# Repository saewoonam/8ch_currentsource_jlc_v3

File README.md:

# 8ch_currentsource_jlc_v3
Second attempt to make an 8 channel current bias board.  
#  Change from v2
- Added a voltage regulator for each channel

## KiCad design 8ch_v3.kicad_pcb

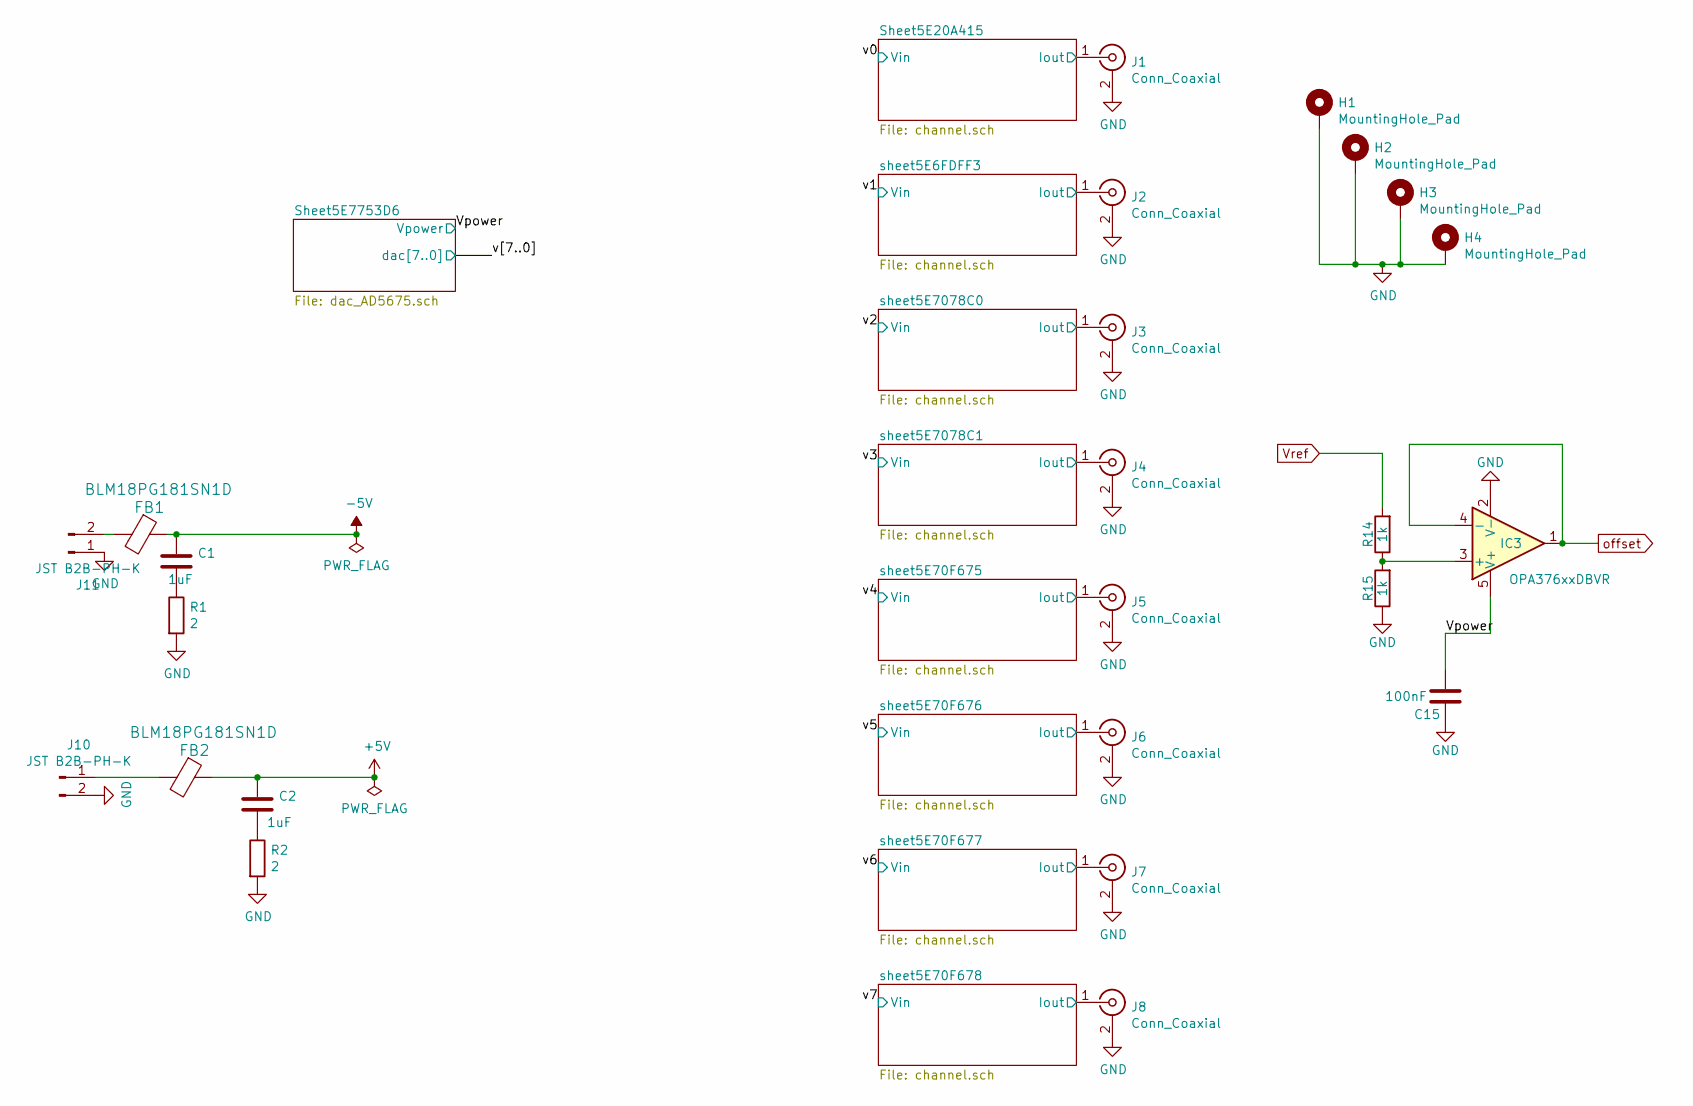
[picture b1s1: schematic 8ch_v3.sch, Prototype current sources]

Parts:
C1, C2: 1uF; C_0603_1608Metric_Pad1.05x0.95mm_HandSolder; MPN CL10B105KA8NNNC
C15: 100nF; C_0603_1608Metric_Pad1.05x0.95mm_HandSolder; MPN CC0603KPX7R7BB104; Digikey 490-1767-1-ND
FB1, FB2: BLM18PG181SN1D; L_0603_1608Metric_Pad1.05x0.95mm_HandSolder; MPN BLM18PG181SN1D
H1, H2, H3, H4: MountingHole_Pad; MountingHole_3.2mm_M3_Pad_Via
IC3: OPA376xxDBVR; SOT-23-5; MPN OPA376AIDBVR
J1, J2, J3, J4, J5, J6, J7, J8: Conn_Coaxial; RF_SMA_Vertical_5-1814832-1; MPN CONSMA001-SMD-G
J10, J11: JST B2B-PH-K; JST_PH_B2B-PH-K_1x02_P2.00mm_Vertical; MPN S2B-PH-SM4
R1, R2: 2; R_0603_1608Metric_Pad1.05x0.95mm_HandSolder; MPN 0603WAF200KT5E
R14, R15: 1k; R_0603_1608Metric_Pad1.05x0.95mm_HandSolder; MPN RC0603FR-071KL

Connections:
+5V: C2.1, FB2.1; also elsewhere on the board
-5V: C1.1, FB1.1; also elsewhere on the board
/Sheet5E20A415/Iout: J1.1 (In); also elsewhere on the board
/Vpower: C15.2, IC3.5 (V+); also elsewhere on the board
/sheet5E6FDFF3/Iout: J2.1 (In); also elsewhere on the board
/sheet5E70F675/Iout: J5.1 (In); also elsewhere on the board
/sheet5E70F676/Iout: J6.1 (In); also elsewhere on the board
/sheet5E70F677/Iout: J7.1 (In); also elsewhere on the board
/sheet5E70F678/Iout: J8.1 (In); also elsewhere on the board
/sheet5E7078C0/Iout: J3.1 (In); also elsewhere on the board
/sheet5E7078C1/Iout: J4.1 (In); also elsewhere on the board
GND: C15.1, H1.1, H2.1, H3.1, H4.1, IC3.2 (V-), J1.2 (Ext), J2.2 (Ext), J3.2 (Ext), J4.2 (Ext), J5.2 (Ext), J6.2 (Ext), J7.2 (Ext), J8.2 (Ext), J10.2, J11.1, R1.2, R2.2, R15.1; also elsewhere on the board
unnamed: C1.2, R1.1
unnamed: C2.2, R2.1
unnamed: FB1.2, J11.2
unnamed: FB2.2, J10.1
unnamed: IC3.3 (+), R14.1, R15.2
Vref: R14.2; also elsewhere on the board
offset: IC3.1, IC3.4 (-); also elsewhere on the board

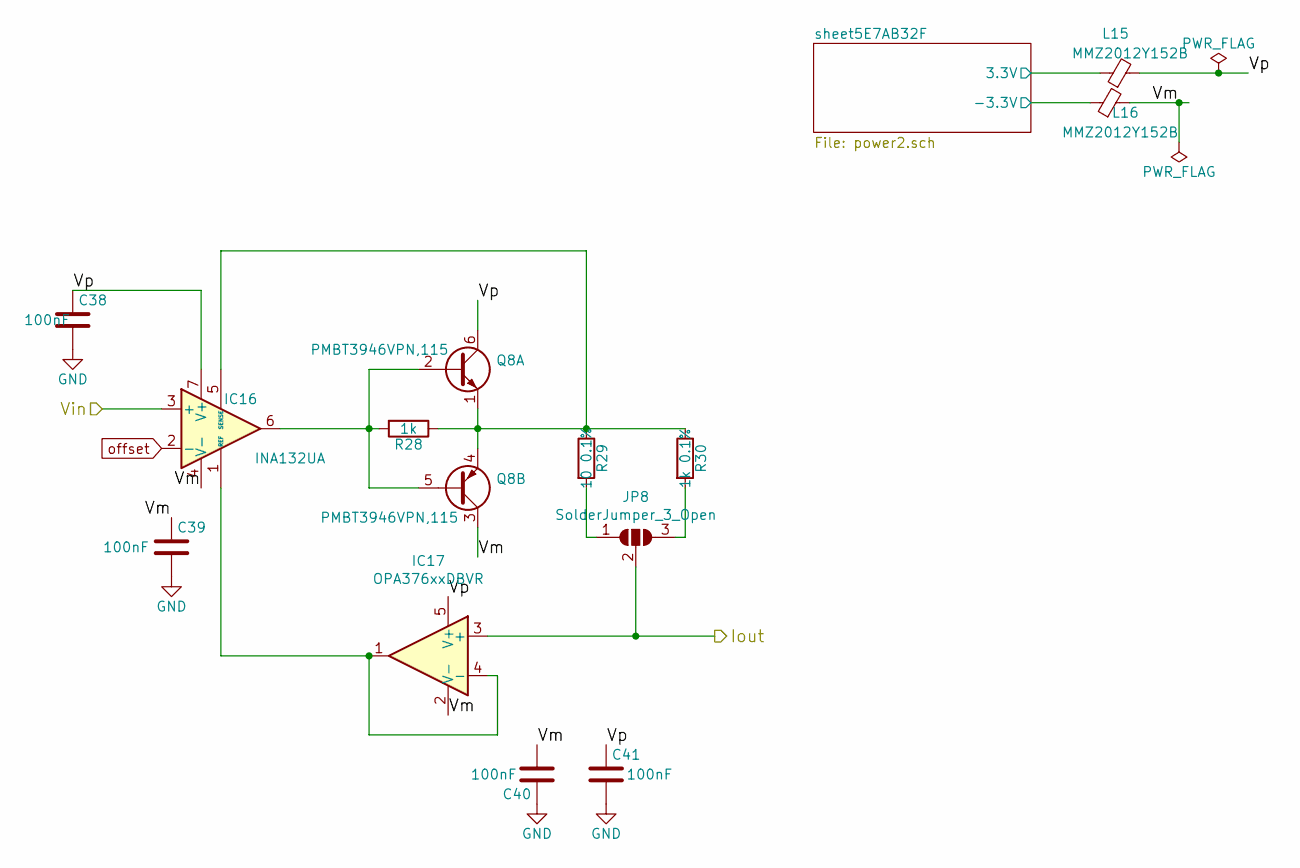
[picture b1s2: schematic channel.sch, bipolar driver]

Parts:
C7, C8, C9, C10: 100nF; C_0603_1608Metric_Pad1.05x0.95mm_HandSolder; Part GRM31C5C1E104JA01L; Digikey 490-1767-1-ND
IC1: INA132UA; SOIC-8_3.9x4.9mm_P1.27mm; MPN-backup AD8276ARMZ; LCSC C38199
IC2: OPA376xxDBVR; SOT-23-5; MPN OPA376AIDBVR; LCSC C42314
JP1: SolderJumper_3_Open; SolderJumper-3_P1.3mm_Open_Pad1.0x1.5mm
L1, L2: MMZ2012Y152B; L_0805_2012Metric_Pad1.15x1.40mm_HandSolder; MPN MMZ2012Y152BTD25
Q1: PMBT3946VPN,115; SOT-363_SC-70-6; MPN MMDT3946-7-F; LCSC C151354
R3: 1k; R_0603_1608Metric_Pad1.05x0.95mm_HandSolder; MPN RC0603FR-071KL
R4: 10 0.1%; R_0805_2012Metric; MPN 2-1625868-7
R5: 1k 0.1%; R_0805_2012Metric; MPN ERA-6AEB102V

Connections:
/Sheet5E20A415/Iout: IC2.3 (+), JP1.2 (C); also elsewhere on the board
/Sheet5E20A415/Vm: C8.1, C9.2, IC1.4 (V-), IC2.2 (V-), L2.2, Q1.3 (C2)
/Sheet5E20A415/Vp: C7.1, C10.1, IC1.7 (V+), IC2.5 (V+), L1.2, Q1.6 (C1)
/Sheet5E20A415/sheet5E7AB32F/3.3V: L1.1; also elsewhere on the board
/Sheet5E20A415/sheet5E7AB32F/-3.3V: L2.1; also elsewhere on the board
/v0: IC1.3 (+); also elsewhere on the board
GND: C7.2, C8.2, C9.1, C10.2; also elsewhere on the board
unnamed: IC1.1 (REF), IC2.1, IC2.4 (-)
unnamed: IC1.5 (SENSE), Q1.1 (E1), Q1.4 (E2), R3.1, R4.1, R5.1
unnamed: IC1.6, Q1.2 (B1), Q1.5 (B2), R3.2
unnamed: JP1.1 (A), R4.2
unnamed: JP1.3 (B), R5.2
offset: IC1.2 (-); also elsewhere on the board

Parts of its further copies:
C11, C12, C16, C17, C18, C19, C20, C21, C22, C23, C24, C25, C26, C27, C28, C29, C30, C31, C32, C33, C34, C35, C36, C37, C38, C39, C40, C41: 100nF; C_0603_1608Metric_Pad1.05x0.95mm_HandSolder; Part GRM31C5C1E104JA01L; Digikey 490-1767-1-ND
IC4, IC6, IC8, IC10, IC12, IC14, IC16: INA132UA; SOIC-8_3.9x4.9mm_P1.27mm; MPN-backup AD8276ARMZ; LCSC C38199
IC5, IC7, IC9, IC11, IC13, IC15, IC17: OPA376xxDBVR; SOT-23-5; MPN OPA376AIDBVR; LCSC C42314
JP2, JP3, JP4, JP5, JP6, JP7, JP8: SolderJumper_3_Open; SolderJumper-3_P1.3mm_Open_Pad1.0x1.5mm
L3, L4, L5, L6, L7, L8, L9, L10, L11, L12, L13, L14, L15, L16: MMZ2012Y152B; L_0805_2012Metric_Pad1.15x1.40mm_HandSolder; MPN MMZ2012Y152BTD25
Q2, Q3, Q4, Q5, Q6, Q7, Q8: PMBT3946VPN,115; SOT-363_SC-70-6; MPN MMDT3946-7-F; LCSC C151354
R6, R9, R16, R19, R22, R25, R28: 1k; R_0603_1608Metric_Pad1.05x0.95mm_HandSolder; MPN RC0603FR-071KL
R7, R10, R17, R20, R23, R26, R29: 10 0.1%; R_0805_2012Metric; MPN 2-1625868-7
R8, R11, R18, R21, R24, R27, R30: 1k 0.1%; R_0805_2012Metric; MPN ERA-6AEB102V

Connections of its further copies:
/sheet5E6FDFF3/Iout: IC5.3 (+), JP2.2 (C); also elsewhere on the board
/sheet5E6FDFF3/Vm: C12.1, C16.2, IC4.4 (V-), IC5.2 (V-), L4.2, Q2.3 (C2)
/sheet5E6FDFF3/Vp: C11.1, C17.1, IC4.7 (V+), IC5.5 (V+), L3.2, Q2.6 (C1)
/sheet5E6FDFF3/sheet5E7AB32F/3.3V: L3.1; also elsewhere on the board
/sheet5E6FDFF3/sheet5E7AB32F/-3.3V: L4.1; also elsewhere on the board
/sheet5E70F675/Iout: IC11.3 (+), JP5.2 (C); also elsewhere on the board
/sheet5E70F675/Vm: C27.1, C28.2, IC10.4 (V-), IC11.2 (V-), L10.2, Q5.3 (C2)
/sheet5E70F675/Vp: C26.1, C29.1, IC10.7 (V+), IC11.5 (V+), L9.2, Q5.6 (C1)
/sheet5E70F675/sheet5E7AB32F/3.3V: L9.1; also elsewhere on the board
/sheet5E70F675/sheet5E7AB32F/-3.3V: L10.1; also elsewhere on the board
/sheet5E70F676/Iout: IC13.3 (+), JP6.2 (C); also elsewhere on the board
/sheet5E70F676/Vm: C31.1, C32.2, IC12.4 (V-), IC13.2 (V-), L12.2, Q6.3 (C2)
/sheet5E70F676/Vp: C30.1, C33.1, IC12.7 (V+), IC13.5 (V+), L11.2, Q6.6 (C1)
/sheet5E70F676/sheet5E7AB32F/3.3V: L11.1; also elsewhere on the board
/sheet5E70F676/sheet5E7AB32F/-3.3V: L12.1; also elsewhere on the board
/sheet5E70F677/Iout: IC15.3 (+), JP7.2 (C); also elsewhere on the board
/sheet5E70F677/Vm: C35.1, C36.2, IC14.4 (V-), IC15.2 (V-), L14.2, Q7.3 (C2)
/sheet5E70F677/Vp: C34.1, C37.1, IC14.7 (V+), IC15.5 (V+), L13.2, Q7.6 (C1)
/sheet5E70F677/sheet5E7AB32F/3.3V: L13.1; also elsewhere on the board
/sheet5E70F677/sheet5E7AB32F/-3.3V: L14.1; also elsewhere on the board
/sheet5E70F678/Iout: IC17.3 (+), JP8.2 (C); also elsewhere on the board
/sheet5E70F678/Vm: C39.1, C40.2, IC16.4 (V-), IC17.2 (V-), L16.2, Q8.3 (C2)
/sheet5E70F678/Vp: C38.1, C41.1, IC16.7 (V+), IC17.5 (V+), L15.2, Q8.6 (C1)
/sheet5E70F678/sheet5E7AB32F/3.3V: L15.1; also elsewhere on the board
/sheet5E70F678/sheet5E7AB32F/-3.3V: L16.1; also elsewhere on the board
/sheet5E7078C0/Iout: IC7.3 (+), JP3.2 (C); also elsewhere on the board
/sheet5E7078C0/Vm: C19.1, C20.2, IC6.4 (V-), IC7.2 (V-), L6.2, Q3.3 (C2)
/sheet5E7078C0/Vp: C18.1, C21.1, IC6.7 (V+), IC7.5 (V+), L5.2, Q3.6 (C1)
/sheet5E7078C0/sheet5E7AB32F/3.3V: L5.1; also elsewhere on the board
/sheet5E7078C0/sheet5E7AB32F/-3.3V: L6.1; also elsewhere on the board
/sheet5E7078C1/Iout: IC9.3 (+), JP4.2 (C); also elsewhere on the board
/sheet5E7078C1/Vm: C23.1, C24.2, IC8.4 (V-), IC9.2 (V-), L8.2, Q4.3 (C2)
/sheet5E7078C1/Vp: C22.1, C25.1, IC8.7 (V+), IC9.5 (V+), L7.2, Q4.6 (C1)
/sheet5E7078C1/sheet5E7AB32F/3.3V: L7.1; also elsewhere on the board
/sheet5E7078C1/sheet5E7AB32F/-3.3V: L8.1; also elsewhere on the board
/v1: IC4.3 (+); also elsewhere on the board
/v2: IC6.3 (+); also elsewhere on the board
/v3: IC8.3 (+); also elsewhere on the board
/v4: IC10.3 (+); also elsewhere on the board
/v5: IC12.3 (+); also elsewhere on the board
/v6: IC14.3 (+); also elsewhere on the board
/v7: IC16.3 (+); also elsewhere on the board
GND: C11.2, C12.2, C16.1, C17.2, C18.2, C19.2, C20.1, C21.2, C22.2, C23.2, C24.1, C25.2, C26.2, C27.2, C28.1, C29.2, C30.2, C31.2, C32.1, C33.2, C34.2, C35.2, C36.1, C37.2, C38.2, C39.2, C40.1, C41.2; also elsewhere on the board
unnamed: IC4.1 (REF), IC5.1, IC5.4 (-)
unnamed: IC4.5 (SENSE), Q2.1 (E1), Q2.4 (E2), R6.1, R7.1, R8.1
unnamed: IC4.6, Q2.2 (B1), Q2.5 (B2), R6.2
unnamed: IC6.1 (REF), IC7.1, IC7.4 (-)
unnamed: IC6.5 (SENSE), Q3.1 (E1), Q3.4 (E2), R9.1, R10.1, R11.1
unnamed: IC6.6, Q3.2 (B1), Q3.5 (B2), R9.2
unnamed: IC8.1 (REF), IC9.1, IC9.4 (-)
unnamed: IC8.5 (SENSE), Q4.1 (E1), Q4.4 (E2), R16.1, R17.1, R18.1
unnamed: IC8.6, Q4.2 (B1), Q4.5 (B2), R16.2
unnamed: IC10.1 (REF), IC11.1, IC11.4 (-)
unnamed: IC10.5 (SENSE), Q5.1 (E1), Q5.4 (E2), R19.1, R20.1, R21.1
unnamed: IC10.6, Q5.2 (B1), Q5.5 (B2), R19.2
unnamed: IC12.1 (REF), IC13.1, IC13.4 (-)
unnamed: IC12.5 (SENSE), Q6.1 (E1), Q6.4 (E2), R22.1, R23.1, R24.1
unnamed: IC12.6, Q6.2 (B1), Q6.5 (B2), R22.2
unnamed: IC14.1 (REF), IC15.1, IC15.4 (-)
unnamed: IC14.5 (SENSE), Q7.1 (E1), Q7.4 (E2), R25.1, R26.1, R27.1
unnamed: IC14.6, Q7.2 (B1), Q7.5 (B2), R25.2
unnamed: IC16.1 (REF), IC17.1, IC17.4 (-)
unnamed: IC16.5 (SENSE), Q8.1 (E1), Q8.4 (E2), R28.1, R29.1, R30.1
unnamed: IC16.6, Q8.2 (B1), Q8.5 (B2), R28.2
unnamed: JP2.1 (A), R7.2
unnamed: JP2.3 (B), R8.2
unnamed: JP3.1 (A), R10.2
unnamed: JP3.3 (B), R11.2
unnamed: JP4.1 (A), R17.2
unnamed: JP4.3 (B), R18.2
unnamed: JP5.1 (A), R20.2
unnamed: JP5.3 (B), R21.2
unnamed: JP6.1 (A), R23.2
unnamed: JP6.3 (B), R24.2
unnamed: JP7.1 (A), R26.2
unnamed: JP7.3 (B), R27.2
unnamed: JP8.1 (A), R29.2
unnamed: JP8.3 (B), R30.2
offset: IC4.2 (-), IC6.2 (-), IC8.2 (-), IC10.2 (-), IC12.2 (-), IC14.2 (-), IC16.2 (-); also elsewhere on the board

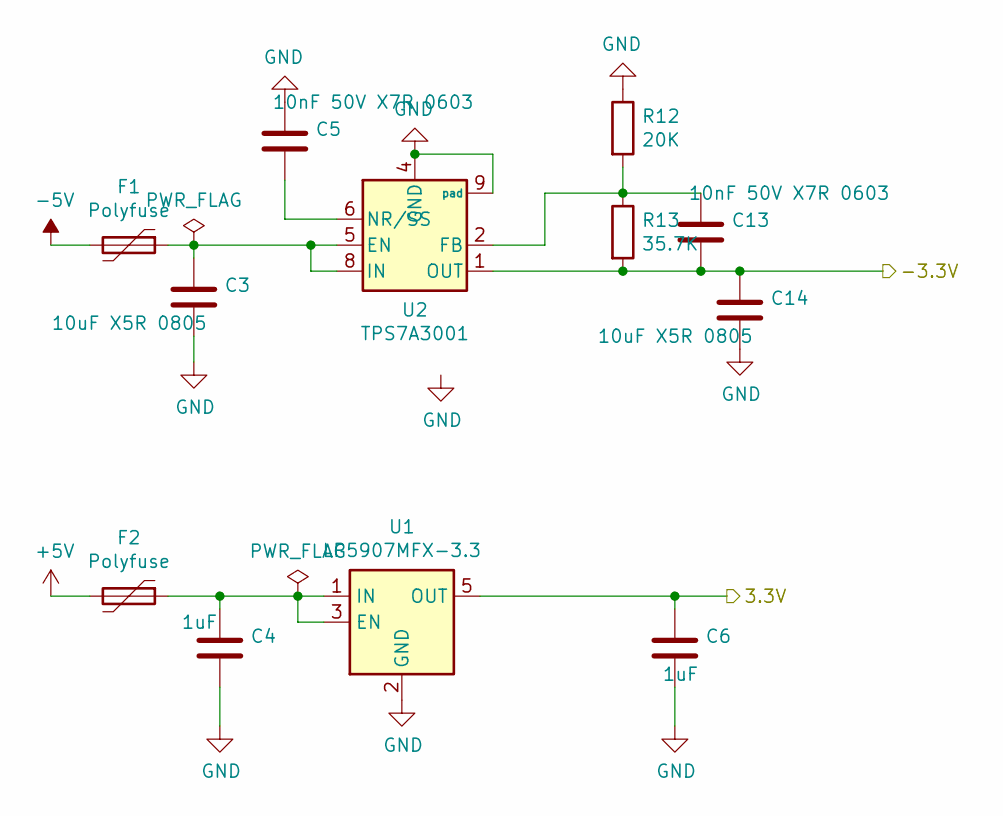
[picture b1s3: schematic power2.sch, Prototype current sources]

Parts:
C3, C14: 10uF X5R 0805; C_0805_2012Metric_Pad1.15x1.40mm_HandSolder; MPN CL31B106KBHNNNE
C4, C6: 1uF; C_0603_1608Metric_Pad1.05x0.95mm_HandSolder; MPN CL10B105KA8NNNC
C5, C13: 10nF 50V X7R 0603; C_0603_1608Metric_Pad1.05x0.95mm_HandSolder; MPN 0603B103K500NT
F1, F2: Polyfuse; Fuse_0603_1608Metric_Pad1.05x0.95mm_HandSolder
R12: 20K; R_0603_1608Metric_Pad1.05x0.95mm_HandSolder; MPN 0603WAF2002T5E
R13: 35.7K; R_0603_1608Metric_Pad1.05x0.95mm_HandSolder; MPN 0603WAF3572T5E
U1: LP5907MFX-3.3; SOT-23-5; MPN LP5907MFX-3.3
U2: TPS7A3001; MSOP-8-1EP_3x3mm_P0.65mm_EP1.68x1.88mm; MPN TPS7A3001DGNR

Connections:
+5V: F2.2; also elsewhere on the board
-5V: F1.2; also elsewhere on the board
/Sheet5E20A415/sheet5E7AB32F/3.3V: C6.1, U1.5 (OUT); also elsewhere on the board
/Sheet5E20A415/sheet5E7AB32F/-3.3V: C13.2, C14.1, R13.2, U2.1 (OUT); also elsewhere on the board
GND: C3.2, C4.2, C5.1, C6.2, C14.2, R12.1, U1.2 (GND), U2.4 (GND), U2.9 (pad); also elsewhere on the board
unnamed: C3.1, F1.1, U2.5 (EN), U2.8 (IN)
unnamed: C4.1, F2.1, U1.1 (IN), U1.3 (EN)
unnamed: C5.2, U2.6 (NR/SS)
unnamed: C13.1, R12.2, R13.1, U2.2 (FB)

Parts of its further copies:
C46, C51, C52, C57, C58, C63, C64, C69, C70, C75, C76, C81, C82, C87: 10uF X5R 0805; C_0805_2012Metric_Pad1.15x1.40mm_HandSolder; MPN CL31B106KBHNNNE
C47, C49, C53, C55, C59, C61, C65, C67, C71, C73, C77, C79, C83, C85: 1uF; C_0603_1608Metric_Pad1.05x0.95mm_HandSolder; MPN CL10B105KA8NNNC
C48, C50, C54, C56, C60, C62, C66, C68, C72, C74, C78, C80, C84, C86: 10nF 50V X7R 0603; C_0603_1608Metric_Pad1.05x0.95mm_HandSolder; MPN 0603B103K500NT
F3, F4, F5, F6, F7, F8, F9, F10, F11, F12, F13, F14, F15, F16: Polyfuse; Fuse_0603_1608Metric_Pad1.05x0.95mm_HandSolder
R33, R35, R37, R39, R41, R43, R45: 20K; R_0603_1608Metric_Pad1.05x0.95mm_HandSolder; MPN 0603WAF2002T5E
R34, R36, R38, R40, R42, R44, R46: 35.7K; R_0603_1608Metric_Pad1.05x0.95mm_HandSolder; MPN 0603WAF3572T5E
U3, U5, U7, U9, U11, U13, U15: LP5907MFX-3.3; SOT-23-5; MPN LP5907MFX-3.3
U4, U6, U8, U10, U12, U14, U16: TPS7A3001; MSOP-8-1EP_3x3mm_P0.65mm_EP1.68x1.88mm; MPN TPS7A3001DGNR

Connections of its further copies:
+5V: F4.2, F6.2, F8.2, F10.2, F12.2, F14.2, F16.2; also elsewhere on the board
-5V: F3.2, F5.2, F7.2, F9.2, F11.2, F13.2, F15.2; also elsewhere on the board
/sheet5E6FDFF3/sheet5E7AB32F/3.3V: C49.1, U3.5 (OUT); also elsewhere on the board
/sheet5E6FDFF3/sheet5E7AB32F/-3.3V: C50.2, C51.1, R34.2, U4.1 (OUT); also elsewhere on the board
/sheet5E70F675/sheet5E7AB32F/3.3V: C67.1, U9.5 (OUT); also elsewhere on the board
/sheet5E70F675/sheet5E7AB32F/-3.3V: C68.2, C69.1, R40.2, U10.1 (OUT); also elsewhere on the board
/sheet5E70F676/sheet5E7AB32F/3.3V: C73.1, U11.5 (OUT); also elsewhere on the board
/sheet5E70F676/sheet5E7AB32F/-3.3V: C74.2, C75.1, R42.2, U12.1 (OUT); also elsewhere on the board
/sheet5E70F677/sheet5E7AB32F/3.3V: C79.1, U13.5 (OUT); also elsewhere on the board
/sheet5E70F677/sheet5E7AB32F/-3.3V: C80.2, C81.1, R44.2, U14.1 (OUT); also elsewhere on the board
/sheet5E70F678/sheet5E7AB32F/3.3V: C85.1, U15.5 (OUT); also elsewhere on the board
/sheet5E70F678/sheet5E7AB32F/-3.3V: C86.2, C87.1, R46.2, U16.1 (OUT); also elsewhere on the board
/sheet5E7078C0/sheet5E7AB32F/3.3V: C55.1, U5.5 (OUT); also elsewhere on the board
/sheet5E7078C0/sheet5E7AB32F/-3.3V: C56.2, C57.1, R36.2, U6.1 (OUT); also elsewhere on the board
/sheet5E7078C1/sheet5E7AB32F/3.3V: C61.1, U7.5 (OUT); also elsewhere on the board
/sheet5E7078C1/sheet5E7AB32F/-3.3V: C62.2, C63.1, R38.2, U8.1 (OUT); also elsewhere on the board
GND: C46.2, C47.2, C48.1, C49.2, C51.2, C52.2, C53.2, C54.1, C55.2, C57.2, C58.2, C59.2, C60.1, C61.2, C63.2, C64.2, C65.2, C66.1, C67.2, C69.2, C70.2, C71.2, C72.1, C73.2, C75.2, C76.2, C77.2, C78.1, C79.2, C81.2, C82.2, C83.2, C84.1, C85.2, C87.2, R33.1, R35.1, R37.1, R39.1, R41.1, R43.1, R45.1, U3.2 (GND), U4.4 (GND), U4.9 (pad), U5.2 (GND), U6.4 (GND), U6.9 (pad), U7.2 (GND), U8.4 (GND), U8.9 (pad), U9.2 (GND), U10.4 (GND), U10.9 (pad), U11.2 (GND), U12.4 (GND), U12.9 (pad), U13.2 (GND), U14.4 (GND), U14.9 (pad), U15.2 (GND), U16.4 (GND), U16.9 (pad); also elsewhere on the board
unnamed: C46.1, F3.1, U4.5 (EN), U4.8 (IN)
unnamed: C47.1, F4.1, U3.1 (IN), U3.3 (EN)
unnamed: C48.2, U4.6 (NR/SS)
unnamed: C50.1, R33.2, R34.1, U4.2 (FB)
unnamed: C52.1, F5.1, U6.5 (EN), U6.8 (IN)
unnamed: C53.1, F6.1, U5.1 (IN), U5.3 (EN)
unnamed: C54.2, U6.6 (NR/SS)
unnamed: C56.1, R35.2, R36.1, U6.2 (FB)
unnamed: C58.1, F7.1, U8.5 (EN), U8.8 (IN)
unnamed: C59.1, F8.1, U7.1 (IN), U7.3 (EN)
unnamed: C60.2, U8.6 (NR/SS)
unnamed: C62.1, R37.2, R38.1, U8.2 (FB)
unnamed: C64.1, F9.1, U10.5 (EN), U10.8 (IN)
unnamed: C65.1, F10.1, U9.1 (IN), U9.3 (EN)
unnamed: C66.2, U10.6 (NR/SS)
unnamed: C68.1, R39.2, R40.1, U10.2 (FB)
unnamed: C70.1, F11.1, U12.5 (EN), U12.8 (IN)
unnamed: C71.1, F12.1, U11.1 (IN), U11.3 (EN)
unnamed: C72.2, U12.6 (NR/SS)
unnamed: C74.1, R41.2, R42.1, U12.2 (FB)
unnamed: C76.1, F13.1, U14.5 (EN), U14.8 (IN)
unnamed: C77.1, F14.1, U13.1 (IN), U13.3 (EN)
unnamed: C78.2, U14.6 (NR/SS)
unnamed: C80.1, R43.2, R44.1, U14.2 (FB)
unnamed: C82.1, F15.1, U16.5 (EN), U16.8 (IN)
unnamed: C83.1, F16.1, U15.1 (IN), U15.3 (EN)
unnamed: C84.2, U16.6 (NR/SS)
unnamed: C86.1, R45.2, R46.1, U16.2 (FB)

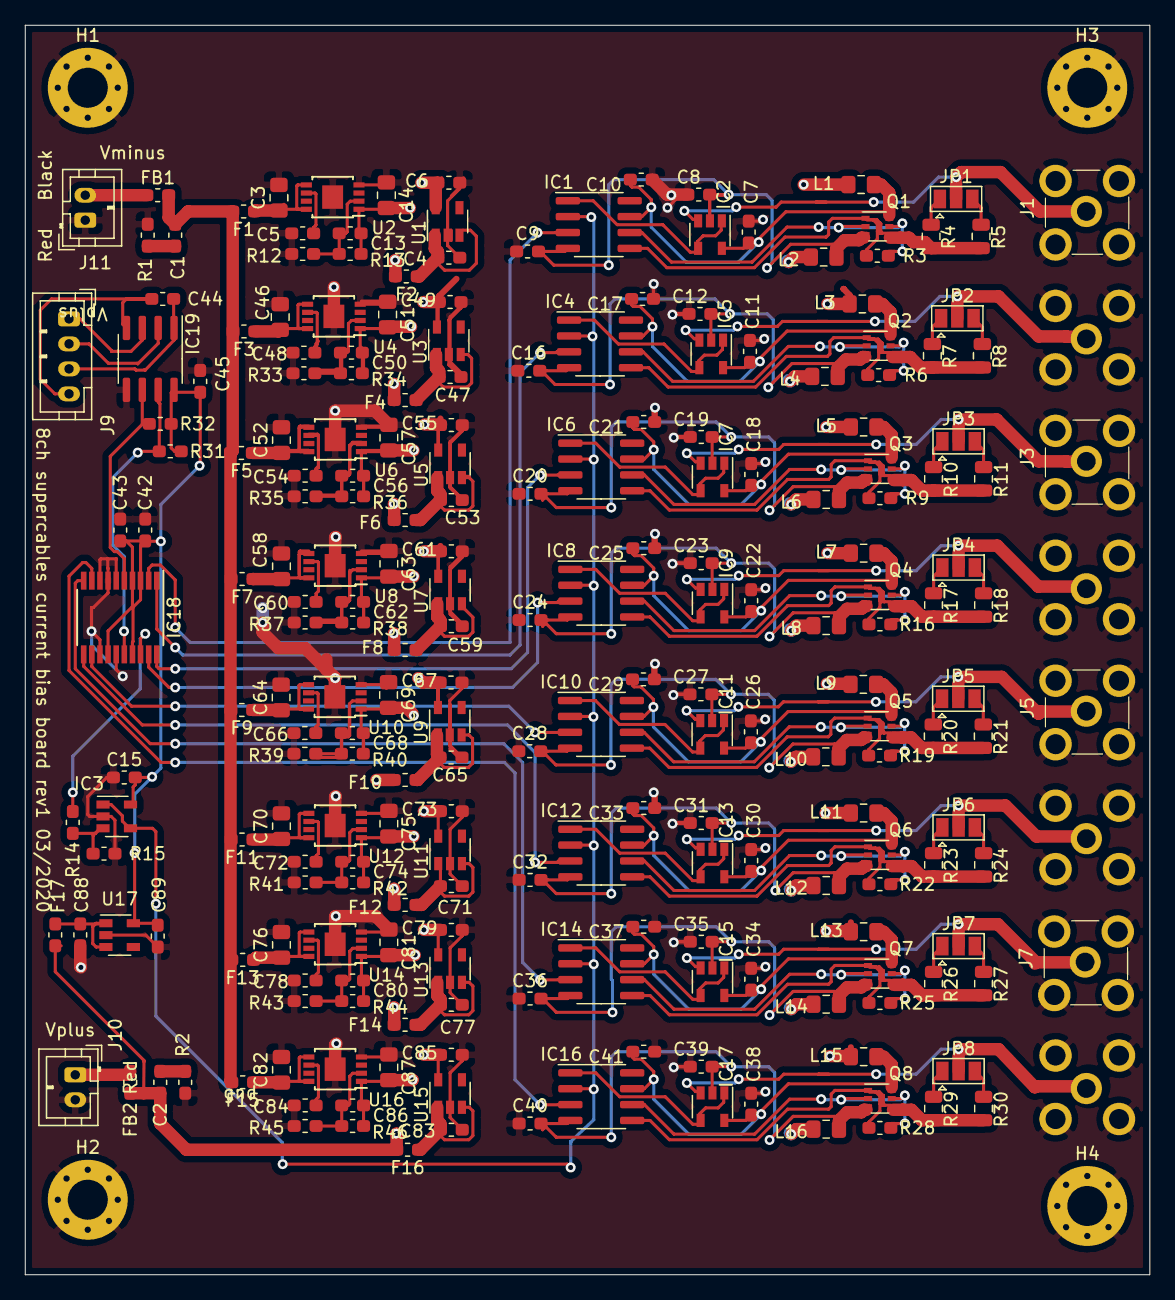
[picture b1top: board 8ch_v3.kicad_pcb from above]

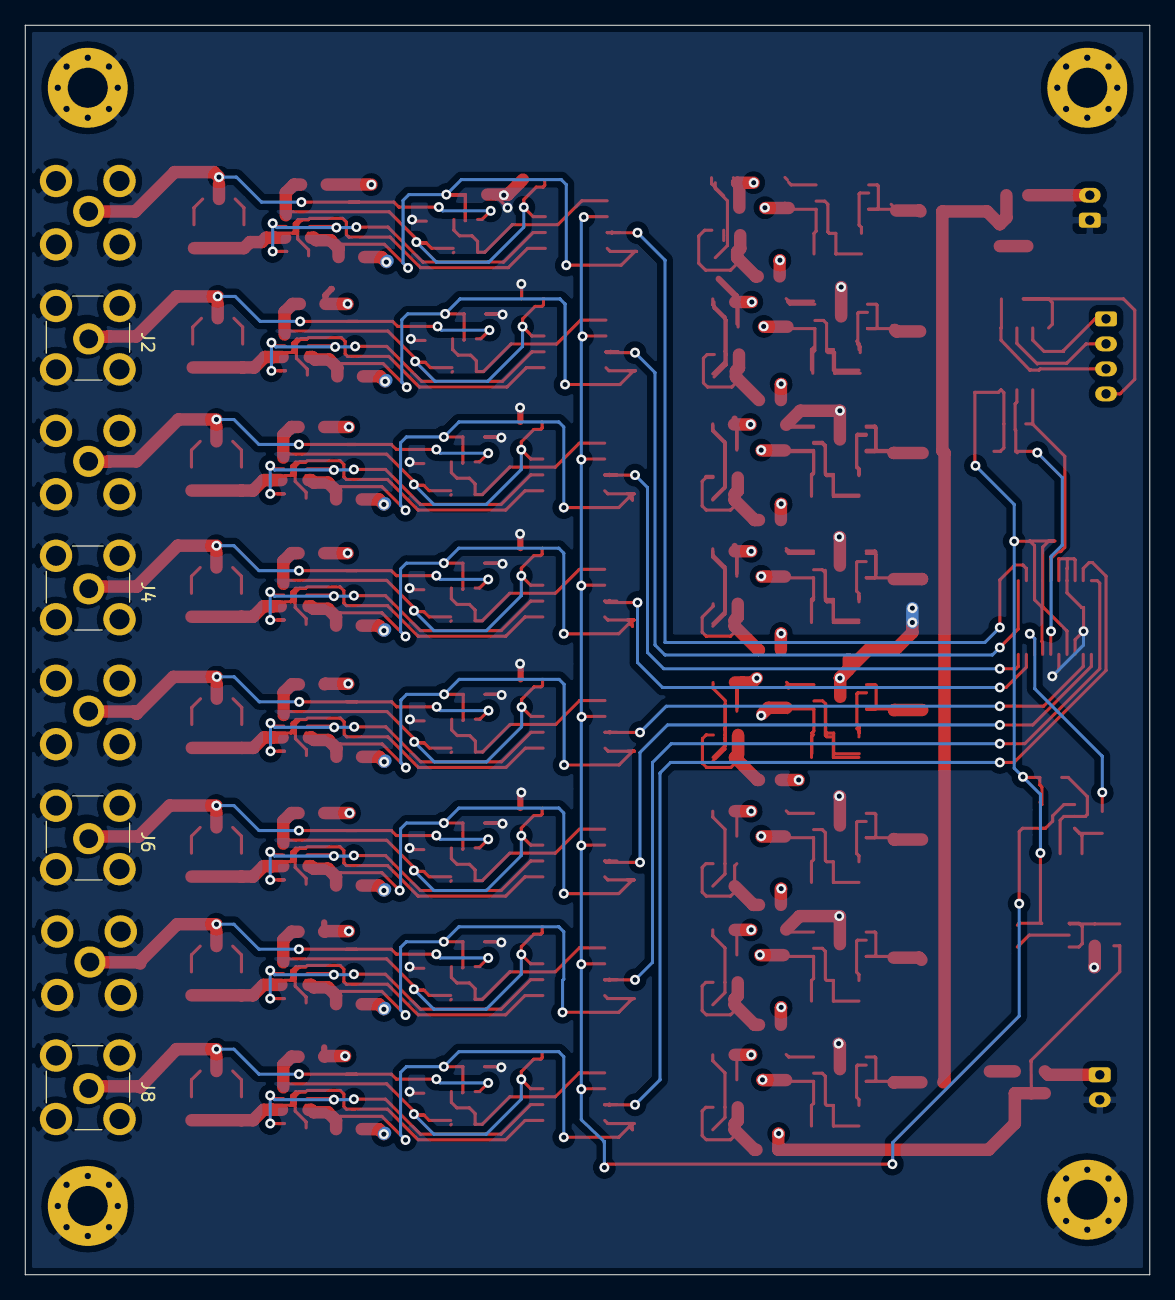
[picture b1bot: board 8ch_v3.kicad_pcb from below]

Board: 4 copper layers, 90.0 x 100.0 mm, 237 parts (4 on the bottom side), 138 nets.

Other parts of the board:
C42, C43, C44, C45: 100nF; C_0603_1608Metric_Pad1.05x0.95mm_HandSolder
C88, C89: 1uF; C_0603_1608Metric_Pad1.05x0.95mm_HandSolder
F17: Polyfuse; Fuse_0603_1608Metric_Pad1.05x0.95mm_HandSolder
IC18: AD5675RBRUZ; TSSOP-20_4.4x6.5mm_P0.65mm
IC19: ISO1541DR; SOIC-8_3.9x4.9mm_P1.27mm
J9: B4B-PH-K; JST_PH_B4B-PH-K_1x04_P2.00mm_Vertical
R31, R32: 10K; R_0603_1608Metric_Pad1.05x0.95mm_HandSolder
U17: LP5907MFX-3.3; SOT-23-5

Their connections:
+5V: F17.2; also elsewhere on the board
/Sheet5E7753D6/Vin: C44.1, IC19.1, J9.3
/Sheet5E7753D6/scl: IC18.5, IC19.6, R32.2
/Sheet5E7753D6/sda: IC18.16, IC19.7, R31.2
/Vpower: C42.2, C43.2, C45.1, C89.1, IC18.3, IC18.4, IC18.14, IC18.17, IC19.8, R31.1, R32.1, U17.5; also elsewhere on the board
/v0: IC18.2; also elsewhere on the board
/v1: IC18.1; also elsewhere on the board
/v2: IC18.20; also elsewhere on the board
/v3: IC18.19; also elsewhere on the board
/v4: IC18.12; also elsewhere on the board
/v5: IC18.11; also elsewhere on the board
/v6: IC18.10; also elsewhere on the board
/v7: IC18.9; also elsewhere on the board
GND: C42.1, C43.1, C45.2, C88.2, C89.2, IC18.6, IC18.7, IC18.8, IC18.13, IC18.15, IC19.5, U17.2; also elsewhere on the board
GNDD: C44.2, IC19.4, J9.4
unnamed: C88.1, F17.1, U17.1, U17.3
unnamed: IC19.2, J9.2
unnamed: IC19.3, J9.1
Vref: IC18.18; also elsewhere on the board

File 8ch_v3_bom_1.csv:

Component,Value,References,SPN,MPN,MFR,Digikey,EXTENDED,BASIC,MFR-backup,MPN-backup,LCSC,Backup,Nxperia
1,100nF,C7 C8 C9 C10 C11 C12 C15 C16 C17 C18 C19 C20 C21 C22 C23 C24 C25 C26 C27 C28 C29 C30 C31 C32 C33 C34 C35 C36 C37 C38 C39 C40 C41 C42 C43 C44 C45,C14663,CC0603KPX7R7BB104,Yageo,490-1767-1-ND,,,,,,,
2,10nF 50V X7R 0603,C5 C13 C48 C50 C54 C56 C60 C62 C66 C68 C72 C74 C78 C80 C84 C86,C57112,0603B103K500NT,Guangdong,,,,,,,,
3,10uF X5R 0805,C3 C14 C46 C51 C52 C57 C58 C63 C64 C69 C70 C75 C76 C81 C82 C87,C15850,CL31B106KBHNNNE,Samsung,,,,,,,,
4,1uF,C1 C2 C4 C6 C47 C49 C53 C55 C59 C61 C65 C67 C71 C73 C77 C79 C83 C85 C88 C89,C15849,CL10B105KA8NNNC,Samsung,,C29936,C15849,,,,,
5,Polyfuse,F1 F2 F3 F4 F5 F6 F7 F8 F9 F10 F11 F12 F13 F14 F15 F16 F17,C261935,,,,,,,,,,
6,BLM18PG181SN1D,FB1 FB2,C82850,BLM18PG181SN1D,Murata,,,,,,,,
7,AD5675RBRUZ,IC18,C393019,AD5675RBRUZ,ADI,,,,,,,,
8,INA132UA,IC1 IC4 IC6 IC8 IC10 IC12 IC14 IC16,C38199,INA132UA/2K5,-,,,,ADI,AD8276ARMZ,C38199,,
9,ISO1541DR,IC19,C143028,ISO1541DR,Texas Instruments,,,,,,,,
10,OPA376xxDBVR,IC2 IC3 IC5 IC7 IC9 IC11 IC13 IC15 IC17,C42134,OPA376AIDBVR,#NAME?,,,,,,C42314,LT6003,
11,B4B-PH-K,J9,-,-,-,,,,,,,,
12,Conn_Coaxial,J1 J2 J3 J4 J5 J6 J7 J8,-,CONSMA001-SMD-G,Linx,,,,,,,,
13,JST S2B-PH-SM4,J10 J11,,S2B-PH-SM4,JST,,,,,,,,
14,SolderJumper_3_Open,JP1 JP2 JP3 JP4 JP5 JP6 JP7 JP8,-,-,-,,,,,,,,
15,MMZ2012Y152B ,L1 L2 L3 L4 L5 L6 L7 L8 L9 L10 L11 L12 L13 L14 L15 L16,C21517,MMZ2012Y152BTD25,TDK,,,,,,,,
16,"PMBT3946VPN,115",Q1 Q2 Q3 Q4 Q5 Q6 Q7 Q8,C28272,MMDT3946-7-F,Diode,,,,,,C151354,,"PMBT3946VPN,115: SOT-666"
17,10 0.1%,R4 R7 R10 R17 R20 R23 R26 R29,C48370,2-1625868-7,TE Connectivity,,,,,,,,
18,10K,R31 R32,C25804,-,-,,,,,,,,
19,1k,R3 R6 R9 R14 R15 R16 R19 R22 R25 R28,C21190,RC0603FR-071KL,Yageo,,,,,,,,
20,1k 0.1%,R5 R8 R11 R18 R21 R24 R27 R30,C54019,ERA-6AEB102V,Panasonic,,,,,,,,
21,2,R1 R2,C22977,0603WAF200KT5E,Uniroyal,,,,,,,,
22,20K,R12 R33 R35 R37 R39 R41 R43 R45,C4184,0603WAF2002T5E,Uniroyal,,,,,,,,
23,35.7K,R13 R34 R36 R38 R40 R42 R44 R46,C23027,0603WAF3572T5E,Uniroyal,,,,,,,,
24,LP5907MFX-3.3,U1 U3 U5 U7 U9 U11 U13 U15 U17,C80670,LP5907MFX-3.3,-,,,,,,,,
25,TPS7A3001,U2 U4 U6 U8 U10 U12 U14 U16,C33835,TPS7A3001DGNR,-,,,,,,,,
,,,,,,,,,,,,,
,,,,,,,,,,,,,
,,,,,,,,,,,,,
,,,,,,,,,,,,,
,,,,,,,,,,,,,
Component Groups:,25,,,,,,,,,,,,
Component Count:,233,,,,,,,,,,,,
Fitted Components:,233,,,,,,,,,,,,
Number of PCBs:,1,,,,,,,,,,,,
Total components:,233,,,,,,,,,,,,
Schematic Version:,1,,,,,,,,,,,,
Schematic Date:,1/25/20,,,,,,,,,,,,
PCB Variant:,[u'default'],,,,,,,,,,,,
BoM Date:,"Thursday, March 26, 2020 at 07:20:16 AM",,,,,,,,,,,,
Schematic Source:,/Users/nams/Documents/projects/kicad/8ch_currentsource_jlc_v3/8ch_v3.sch,,,,,,,,,,,,
KiCad Version:,Eeschema (5.1.5-0),,,,,,,,,,,,

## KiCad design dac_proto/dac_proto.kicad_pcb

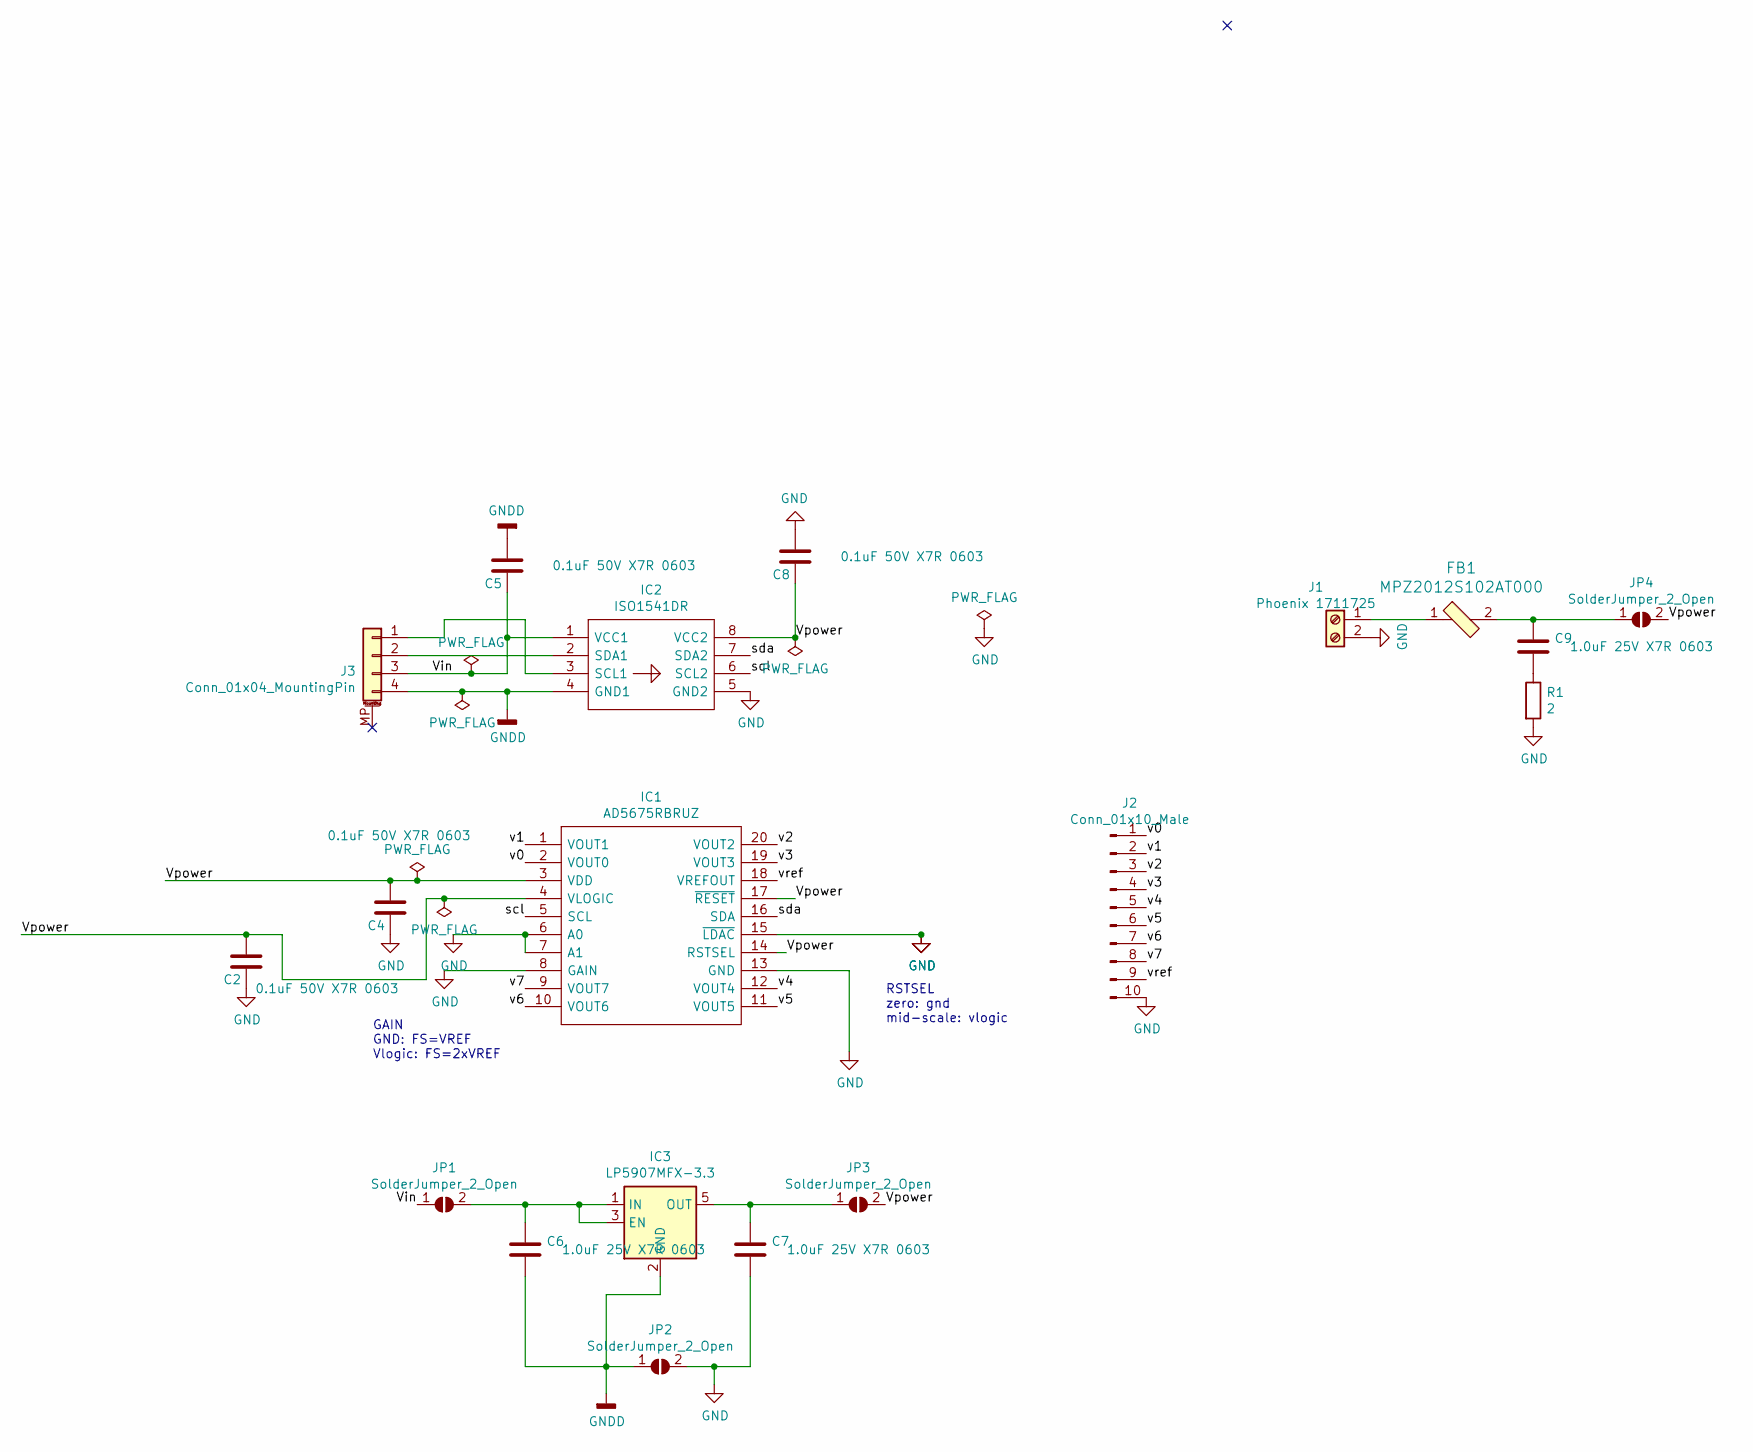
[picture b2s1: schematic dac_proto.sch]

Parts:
C2, C4, C5, C8: 0.1uF 50V X7R 0603; C_0603_1608Metric_Pad1.05x0.95mm_HandSolder; Part CC0603KRX7R9BB104; Digikey 490-1767-1-ND
C6, C7, C9: 1.0uF 25V X7R 0603; C_0603_1608Metric_Pad1.05x0.95mm_HandSolder; MPN CL10B105KA8NNNC
FB1: MPZ2012S102AT000; 0805; MPN MPZ2012S102AT000; Digi-Key_PN 445-5223-1-ND
IC1: AD5675RBRUZ; TSSOP-20_4.4x6.5mm_P0.65mm; MPN AD5675RBRUZ
IC2: ISO1541DR; SOIC-8_3.9x4.9mm_P1.27mm; MPN ISO1541DR
IC3: LP5907MFX-3.3; SOT-23-5; MPN LP5907MFX-3.3
J1: Phoenix 1711725; TerminalBlock_Phoenix_MKDS-3-2-5.08_1x02_P5.08mm_Horizontal; MPN 1711725
J2: Conn_01x10_Male; PinHeader_1x10_P2.54mm_Vertical
J3: Conn_01x04_MountingPin; JST_PH_S4B-PH-SM4-TB_1x04-1MP_P2.00mm_Horizontal
JP1, JP2, JP3, JP4: SolderJumper_2_Open; SolderJumper-2_P1.3mm_Open_RoundedPad1.0x1.5mm
R1: 2; R_0603_1608Metric_Pad1.05x0.95mm_HandSolder; MPN 0603WAF200KT5E

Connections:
/Vin: C5.1, IC2.1 (VCC1), J3.3, JP1.1 (A)
/Vpower: C2.2, C4.2, C8.1, IC1.3 (VDD), IC1.4 (VLOGIC), IC1.14 (RSTSEL), IC1.17 (~RESET), IC2.8 (VCC2), JP3.2 (B), JP4.2 (B)
/scl: IC1.5 (SCL), IC2.6 (SCL2)
/sda: IC1.16 (SDA), IC2.7 (SDA2)
/v0: IC1.2 (VOUT0), J2.1
/v1: IC1.1 (VOUT1), J2.2
/v2: IC1.20 (VOUT2), J2.3
/v3: IC1.19 (VOUT3), J2.4
/v4: IC1.12 (VOUT4), J2.5
/v5: IC1.11 (VOUT5), J2.6
/v6: IC1.10 (VOUT6), J2.7
/v7: IC1.9 (VOUT7), J2.8
/vref: IC1.18 (VREFOUT), J2.9
GND: C2.1, C4.1, C7.2, C8.2, IC1.6 (A0), IC1.7 (A1), IC1.8 (GAIN), IC1.13 (GND), IC1.15 (~LDAC), IC2.5 (GND2), J1.2, J2.10, JP2.2 (B), R1.2
GNDD: C5.2, C6.2, IC2.4 (GND1), IC3.2 (GND), J3.4, JP2.1 (A)
unnamed: C6.1, IC3.1 (IN), IC3.3 (EN), JP1.2 (B)
unnamed: C7.1, IC3.5 (OUT), JP3.1 (A)
unnamed: C9.1, FB1.2, JP4.1 (A)
unnamed: C9.2, R1.1
unnamed: FB1.1, J1.1
unnamed: IC2.2 (SDA1), J3.2
unnamed: IC2.3 (SCL1), J3.1

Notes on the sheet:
GAIN GND: FS=VREF Vlogic: FS=2xVREF
RSTSEL zero: gnd mid-scale: vlogic

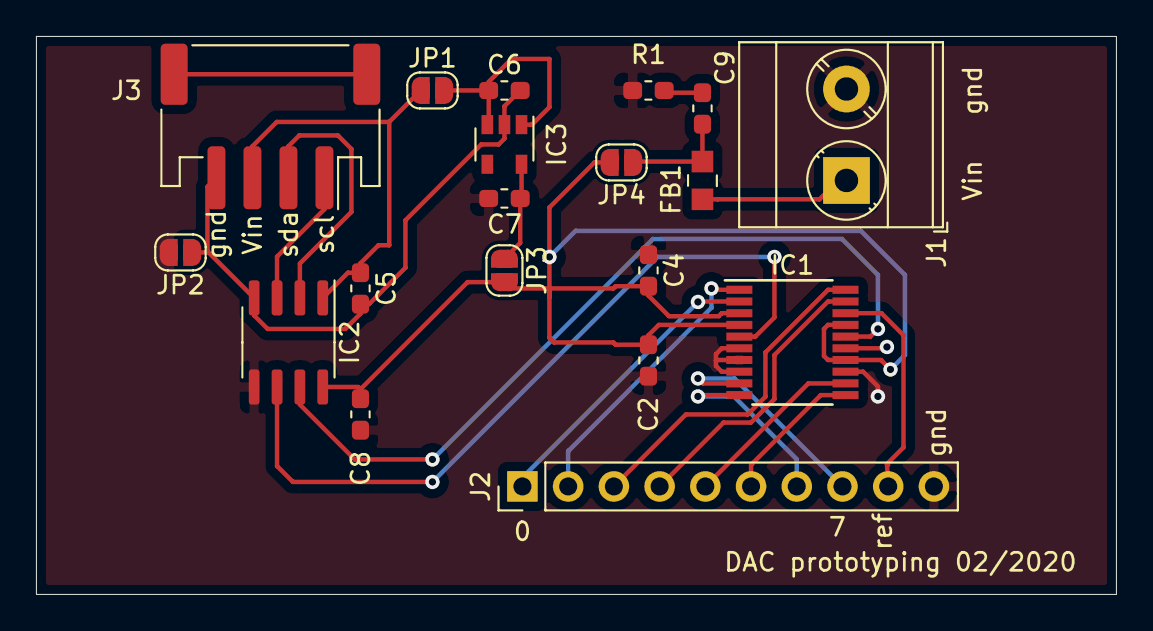
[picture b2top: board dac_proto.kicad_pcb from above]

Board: 2 copper layers, 60.0 x 31.0 mm, 19 parts (0 on the bottom side), 22 nets.

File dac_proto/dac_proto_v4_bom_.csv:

Designator,Comment,Footprint,SPN
C2 C4 C5 C8,0.1uF 50V X7R 0603,C_0603_1608Metric_Pad1.05x0.95mm_HandSolder,C14663
C6 C7 C9,1.0uF 25V X7R 0603,C_0603_1608Metric_Pad1.05x0.95mm_HandSolder,C29936
FB1,MPZ2012S102AT000,805,C21519
IC1,AD5675RBRUZ,TSSOP-20_4.4x6.5mm_P0.65mm,C393019
IC2,ISO1541DR,SOIC-8_3.9x4.9mm_P1.27mm,C143028
IC3,LP5907MFX-3.3,SOT-23-5,C143028
J3,Conn_01x04_MountingPin,JST_PH_S4B-PH-SM4-TB_1x04-1MP_P2.00mm_Horizontal,
J2,Conn_01x10_Male,PinHeader_1x10_P2.54mm_Vertical,
J1,Phoenix 1711725,TerminalBlock_Phoenix_MKDS-3-2-5.08_1x02_P5.08mm_Horizontal,C89120
JP1 JP2 JP3 JP4,SolderJumper_2_Open,SolderJumper-2_P1.3mm_Open_RoundedPad1.0x1.5mm,
R1,2,R_0603_1608Metric_Pad1.05x0.95mm_HandSolder,C22977
